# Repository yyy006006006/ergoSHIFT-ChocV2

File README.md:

# nekoko Choc V2 Edition (based on ergoSHIFT Rev1)

This derivative of ergoSHIFT Rev1 adds a PCB designed for Kailh Choc V1 / V2 switches and Choc V2 button caps.
Modified and distributed by **nekoko / [yyy006006006](https://github.com/yyy006006006)**.
This does not imply an official product or endorsement by the original author.

| Files | Description |
| --- | --- |
| [KiCad PCB source](./hardware-rev1/design_data/ergoSHIFT-rev1-ChocV1-V2-Standard-BSocket-kicad/) | Rev1-based Choc V1 / V2 PCB with the standard right-handed layout. Mount switches on the front and hot-swap sockets on the back. |
| [PCB manufacturing Gerber ZIP](./hardware-rev1/ergoSHIFT-rev1-ChocV1-V2-Standard-BSocket-gerber.zip) | Manufacturing files for this modified PCB, separate from the original Rev1 Gerbers. |
| [Choc V2 button caps](./3d-printed-buttoncaps/#choc-v2-button-caps-added-by-nekoko) | Use 14 small caps and 1 large cap. STL files, editable STEP files, and the generation script are provided. |
| [Web button configurator source](./web-configurator/) | Visual USB remapping for 11 large buttons. Requires the [nekoko configuration firmware](./firmwares_atmega32u4/LUFA/#nekoko-web-configuration-firmware-experimental) on an ATmega32U4 controller. Firmware and web app: GPL v3. |

The original Rev1 board outline, key centers, mounting holes, and MCU connections are unchanged.
This PCB is for back-mounted sockets only; direct switch soldering and reversed/left-handed assembly are not supported.
Choc V1 and V2 use different cap mounts, so choose cap files that match your switches.
The Choc V2 caps have been checked in CAD; physical printed fit and case clearance have not been tested.
See the [Rev1 notes](./hardware-rev1/#nekoko-edition-choc-v1--v2-pcb) for remaining PCB validation findings.

**Original design and license:** ergoSHIFT (c) by [mizma](https://github.com/mizma/ergoSHIFT).
This repository copies [Darudado/ergoSHIFT_RGB](https://github.com/Darudado/ergoSHIFT_RGB) at commit `8f152af28f62ab4e4357ed43b05d77b5a4bff9c2`, with the files and documentation above added on 2026-10-18.
The original designs, attribution, and license notices are retained. The PCB and cap modifications are also released under [CC BY-SA 4.0](https://creativecommons.org/licenses/by-sa/4.0/).
See [LICENSE](./LICENSE) for the full terms. Firmware and component libraries retain their respective licenses and attribution notices.

[Full license texts and notices](./LICENSES.txt) are included in source downloads. The firmware's [build instructions and bundled dependency sources](./firmwares_atmega32u4/LUFA/#source-download-and-rebuild) are provided with the modified firmware source. No personal contact information is required to download these materials.

The original repository documentation follows. Its Rev2, RGB, and reversed-assembly descriptions apply to the upstream versions, not this modified PCB.

---

ergoSHIFT arcade controller
========================================================================

_**Low profile 11 button leverless arcade controller with Acrylic shell**_

This repository contains Acrylic cut design files, PCB design files and code needed to make
an arcade controller that look like this:

Also, you can create custom artwork using the stencil provided in each hardware revision folder.

(*) Above sample Artwork based on an In-Game Screenshot + Official Fan-kit (©Cygames & ARK SYSTEM WORKS)

This controller is designed with the following concept:

* Create a reasonably compact and thin leverless arcade controller
* Layout 11 main buttons + 4 directional buttons to work with the latest 
  Capcom Pro-Tour rule-set
* Shift the home position for the main button one column to the right to better utilize the 
  more dextrous thumb and index finger instead of the little finger.
* Add the three additionally allowed buttons
* Make the button size compatible with Snackbox MICRO from [Junkfood Arcades](https://junkfoodarcades.com/)
    * I could not find good Injection molded options other than this one.
* Make the design reversible for southpaw use.
    * To assemble for left hand use, implement all buttons on the other side.
    * Controller Circuit (Pro Micro or RP2040) must be implemented on the same side
    * to compensate for the Controller Cicuitry being implemented in reverse, Acrylic layers will need to be 
      stacked in a different order and thickness.  Refer to each revision README for details

Resulting button mappings will look like this:

There are currently two revisions of the ergoSHIFT.  It uses Kailh low profile (choc v1)
mechanical keyboard switches.  The table below lists their main features.
See the README for each version for details on how to make them.

version                                 | [rev1](./hardware-rev1/)            | [rev2](./hardware-rev2/)              | [rgb](./hardware-rgb/)                | 
--------------------------------------- | ----------------------------------- | ------------------------------------- | ------------------------------------- | 
Status                                  | Verified                            | Verified                              | Verified                              | 
case dimensions                         | 233.17x147.67x14.6mm (excl. feet)   | 233.17x147.67x14.6mm (excl. feet)     | 233.17x147.67x14.6mm (excl. feet)     | 
compatibility (using provided firmware) | PC, PS3, Xinput, Switch             | PC, PS3, PS4*, PS5*, Xinput, Switch   | PC, PS3, PS4*, PS5*, Xinput, Switch   | 
add-on board                            | Sparkfun Qwiic Pro Micro            | SSD1306, SH1106 or SH1107 128x64 oled | SSD1306, SH1106 or SH1107 128x64 oled | 
onboard chip                            | -                                   | RP2040                                | RP2040                                | 
port                                    | USB-C                               | USB-C                                 | USB-C                                 | 
SMT assembly required                   | no                                  | yes                                   | yes                                   | 
OLED Support                            | no                                  | yes                                   | yes                                   | 
RGB Support                             | no                                  | no                                    | yes                                   | 
South-paw support                       | yes                                 | yes                                   | no                                    | 
firmware                                | [ATmega32U4](firmwares_atmega32u4)  | [GP2040-CE](https://gp2040-ce.info/)**| [GP2040-CE](https://gp2040-ce.info/)**| 

*) for details, see the documentation in the [GP2040-CE Console Compatibility FAQ](https://gp2040-ce.info/faq/faq-console-compatibility/)

**) Firmware is available from the official [GP2040-CE Website](https://gp2040-ce.info/downloads)
See [GP2040 firmware page](./firmware_GP2040-CE/) for firmware with ergoSHIFT specific patches (i.e. OLED display layout patch)

LICENSE
------------------------------------------------------------------------

ergoSHIFT (c) by mizma

ergoSHIFT is licensed under a
Creative Commons Attribution-ShareAlike 4.0 International License.

You should have received a copy of the license along with this
work. If not, see <https://creativecommons.org/licenses/by-sa/4.0/>.

Some portions of the work uses derivative works of other libraries and or implementations.
Firmware and hardware designs are separately licensed depending on the licensing terms of 
the works it uses.  Refer to the LICENSE files or README for the relevant terms for each
component.

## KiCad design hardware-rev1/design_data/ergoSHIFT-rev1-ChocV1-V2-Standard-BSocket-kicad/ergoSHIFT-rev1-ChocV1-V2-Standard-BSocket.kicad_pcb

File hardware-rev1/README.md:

## nekoko edition: Choc V1 / V2 PCB

For this modified PCB, use the [KiCad source](./design_data/ergoSHIFT-rev1-ChocV1-V2-Standard-BSocket-kicad/) and [Gerber ZIP](./ergoSHIFT-rev1-ChocV1-V2-Standard-BSocket-gerber.zip).
Mechanical holes for Kailh Choc V1 / V2 and a back-only socket footprint have been added, preserving the original outline, key positions, mounting holes, and MCU connections.
This is the standard right-handed layout only. Mount switches on the front and 15 Kailh CPG135001S30 sockets on the back.
Direct switch soldering is not supported, and the original reversed-assembly instructions do not apply to this version.
The MCU footprint is for an ATmega32U4 Pro Micro. Use the existing [Rev1 firmware](../firmwares_atmega32u4/), rather than the RP2040 firmware for Rev2.

Saved validation results from 2026-10-02 show 0 DRC errors, 0 unconnected items, and 0 schematic/PCB parity findings.
Remaining findings are 34 DRC warnings (6 silkscreen-to-edge clearance, 4 library footprint mismatches, and 24 silkscreen-over-copper), 1 ERC error (power pin not driven), and 21 ERC warnings.
No check exclusions were added and no rules were relaxed. These results do not establish that every physical button works or that every switch and case will fit.

Modified by nekoko / [yyy006006006](https://github.com/yyy006006006); prepared for publication on 2026-10-18.
Original design: ergoSHIFT (c) by [mizma](https://github.com/mizma/ergoSHIFT). The modified design is also licensed under [CC BY-SA 4.0](https://creativecommons.org/licenses/by-sa/4.0/).
The original Rev1 documentation follows.

---

ergoSHIFT rev1
========================================================================

This is rev1 of the ergoSHIFT.  In this version an Arduino Pro Micro
is soldered onto the main PCB.

To make one you will need:

* [acrylic shell](./acrylic-shell/)
    * For Standard Layout
        * Layers 1, 2, 4: 3mm
        * Layers 3, 5: 2mm
    * For Reverse Layout (Left handed)
        * Layers 1, 2, 3: 3mm
        * Layers 4, 5: 2mm
* [the ergoSHIFT PCB](./pcb/)
* Arduino Pro Micro [SparkFun Qwiic Pro Micro - USB-C (ATmega32U4)](https://www.sparkfun.com/products/15795)
* 15x Kailh low profile (choc v1) switches of your choice
    * I use Kailh Choc v1 Red Pro (Linear and low activation force: 35±10gf with actuation travel: 1.5±0.5mm)
    * Light Blue (gChoc) can be used for even lower actuation force.
* (optionally) 15x Kailh low profile hotswap sockets
* Button Caps (Choose one)
    * [MICRO keycap set](https://junkfoodarcades.com/collections/micro-accessories)
        * You will need to buy two sets of Snackbox Micro keycap sets.
    * [3D printed buttoncaps](../3d-printed-buttoncaps)
* 3x 6x6x8.51mm tact switches
    * I Used [TE Connectivity 3-1825910-5](https://www.te.com/ja/product-3-1825910-5.html)
* 1x 3x6x4.3 horizontal tact switch
    * https://www.newegg.com/p/2S7-01KR-035X0
    * https://shop.yushakobo.jp/collections/all-keyboard-parts/products/a1600ed-01-1
    * [schematics](images/tactile-switch_3x6x4.3.jpg)
* 7x M3 screws (length 20mm)
    * Acryl top 2mm * 2 + 3mm = 7mm
    * PCB 1.6mm
    * Acryl bottom 3mm * 2 = 6mm
    * Rubber feet screw depth = 3mm (using rubber feet below.  adjust for your part)
    * Rubber feet total depth = 8mm (using rubber feet below.  adjust for your part)
    * M3 nut height = 2mm
    * min length = 19.6mm (using rubber feet below.  adjust for your part)
    * max length = 22.6mm (using rubber feet below.  adjust for your part)
* 7x M3 nut and acompanying rubber feet
    * Rubber feet Tochigiya [TM-TK-15](https://www.monotaro.com/p/0933/2486/?displayId=5)
    * The position of the holes are intended for feet radius of less than 8mm
* Some Tin coated wires
* a soldering iron
    * something with enough power is better 
      (i.e. [Hakko FX 600](https://www.hakko.com/japan/products/hakko_fx600_set.html))
    * I recommend changing tips to D type for most Through-hole soldering, or C type if you plan to
      solder SMT as well. (default B tips are harder to use for most PCB soldering)
    * Use 320C ~ 370C temp recommended (can be changed if you know your way around)

## Assembly Instructions

### Ordering PCB

I used [JLCPCB](https://jlcpcb.com/).  Just upload the gerber files in [pcb](pcb) and keep most parameters default.
You may change PCB Qty and PCB Color if you like.  All other parameters should be kept the same.

### Ordering Buttons

#### Snackbox Micro button caps

ergoSHIFT is compatible with Snackbox Micro button caps.

You can purchase them [HERE](https://junkfoodarcades.com/collections/micro-accessories)

#### 3D printed buttons

_**Currently verifying design**_

If you have a 3D printer, print at your own will.  Files are found [here](../3d-printed-buttoncaps/).

* [ergoSHIFT-ButtonCapBig.stl](../3d-printed-buttoncaps/ergoSHIFT-ButtonCapBig.stl) 
  is used for the thumb button. 1 board needs 1 of this button.
* [ergoSHIFT-Buttoncap.stl](../3d-printed-buttoncaps/ergoSHIFT-ButtonCapBig.stl) is used for all other buttons.
  1 board needs 14 of this button.
* [ergoSHIFT-FullSetButtonCaps.stl](../3d-printed-buttoncaps/ergoSHIFT-FullSetButtonCaps.stl) is an STL file 
  containing 1 full set of buttons + extra(26 small and 2 big.).  If your 3D printing service allows 28 or more shells, it may be cheaper to print in one batch using this STL file.
    * Print size needs to be bigger than X：99.4901mm x Y： 91.7951mm x Z： 15.0000mm
    * To accomodate for the buttons in the 100mm x 100mm x 100mm size limit in some Printing services,
      This STL file has two layers of buttons arranged on top of each other.  This type of layout is only
      possible on print technology such as SLS or MJF.  Check with your 3D Printing service.
    * If your 3D Printing service does not support this type of data, use individual cap data to print.

Insertion portion may need to be adjusted in size for your 3D Printer and settings to fit snugly to the switch.
You may use some of the printer features but if that doesn't work, you might want to edit the original model.
Model data are found in [here](../3d-printed-buttoncaps/design_data/) in a [FreeCAD](https://www.freecadweb.org/)
file format.

Also, since the insertion portion requires a fairly tight tolerance which is not easily achieved by 3D printers,
the models are modelled slightly on the larger side.

I have had fairly good results with this model using SLS/MJF Nylon print but sometimes it is too large.
If the legs turn out too large to fit, use sandpaper to adjust the width of the legs.

#### Materials Consideration

* Nylon
    * May be a good place to start for tensile strength and good chemical stability.
    * can be pretty strong if printed using SLS process at some printing services
    * may be prone to warping.  not good for humid places.
* UV Resin
    * Also pretty strong as a material, and stronger to humidity.
    * Maybe slightly more brittle than Nylon

### Ordering Acrylic cuts

I use [Elecrow](https://www.elecrow.com/acrylic-cutting.html) to cut acrylic.

Upload the .zip file in [acrylic-shell](acrylic-shell/) to the Elecrow Acrylic cut service to order.
.Zip file includes the dxf file and the dimentions.txt file.  PDF is just for reference.

Use the following thickness:

* For Standard Layout
    * Layers 1, 2, 4: 3mm
    * Layers 3, 5: 2mm
* For Reverse Layout (Left handed)
    * Layers 1, 2, 3: 3mm
    * Layers 4, 5: 2mm

The original design file (FreeCAD file) can be found [here](./design_data/acryl-design/).

The Acrylic should look like the following (with PCB stacked)

(*) Above image is for standard layout (right handed)

### Assembly

1. Solder all the Choc v1 switches and the tactile switches.  make sure you populate the side with the logo.
    * If you populate the side with the logo on the left, the parts only goes in in the correct orientation.
        * For reverse layout, implement the buttons on the other side as shown in [this picture](images/Reverse-Layout-Solering.jpg)
    * If you use the hot-swap sockets, those will go on the back. (see silk screen on back side for orientation)
        * For hotswap sockets, pre-solder one side of the pad on PCB, place the socket, heat the pre-solder while
          pressing down on the socket to attach the socket.  After It is attached, solder the other side fully and then add more solder on the pre-soldered side.
2. Solder the Pro Micro Qwiic from the bottom side of the PCB up into the slit (USB socket should be between the cut-outs on the board, facing up) (Following instruction is how I did it.  There may be other ways) (This should NOT BE REVERSED for left hand layout)
    1.  First, mask the back side holes on the PCB with masking tape, and poke a small hole in each Through-hole with a needle. (This is to stop creating solder filets on the side the ProMicro will be soldered to.
        
    2. Insert a short (2~3cm) tin coated wire in the hole and solder onto the board.  Then cut the excess wire on the front side.

    3. Remove the masking tape.  The back side should have a flat solder filled hole with wires coming out the middle.
       
    4. Place the Pro-Micro into the wires, tape it down to place.  Also tape the entire front side of 
       the soldered through-holes so the wires don't fall when solder melts.
       
    5. Solder the Pro-Micro to the tin-coated wire.
       
3. stack the Acryl and PCB in following order: Layer 01, Layer 02, PCB, Layer 03, Layer 04 and Layer 05.
    * If you use 2 Layer 4s, the order should be 01, 02, 03, 04, 04.
4. Screw on the M3 screws with the nut on all 7 locations.  Rubber feet should be inserted at least in the 4 corners between the nut and the acrylic.

It should look like the following when assembled.

### Pro-Tip 1. Filing the Acrylic Edges

Acrylic Edges after laser cutting can be quite sharp and do not feel good.
You may want to file the edges with sandpaper (#400 is a nice place to start) to remove the edges 
on the top acrylic layer so it does not feel bad.

### Pro-Tip 2. Customizing design

You can also insert some artwork below the top acrylic layer as below:

(*) Above sample Artwork based on an In-Game Screenshot + Official Fan-kit (©Cygames & ARK SYSTEM WORKS)

Stencil for the artwork can be found below (Page size set to A4):

* [Stencil SVG](./images/ergoSHIFT-stencil.svg)
* [Stencil PNG 300dpi](./images/ergoSHIFT-stencil.png)
* [Southpaw Stencil SVG](./images/ergoSHIFT-stencil-reverse.svg)
* [Southpaw Stencil PNG 300dpi](./images/ergoSHIFT-stencil-reverse.png)

To cut the stencil, use one of the top acrylic plates as cutting guides (don't trust the acuracy
of the printed stencil mark, they are good enough to use as design guide, but not acurate enough for 
final cutting guide).  It is easy to cut if you tape the plate on top of the print and use a sharp
designers knife.

## License and Acknowlegements

PCB design licensed under [CC BY-SA 4.0](https://creativecommons.org/licenses/by-sa/4.0/) by mizma

Acrylic sandwitching shell heavily inspired by [Mille-Feuille](https://pomegd.booth.pm/items/2685530) 
by [@pomegd](https://twitter.com/pomegd)

PCB design uses the following libraries or derivatives of the design:

* [keyswitches.pretty](https://github.com/daprice/keyswitches.pretty) by [daprice](https://github.com/daprice) ([CC BY-SA 4.0](https://creativecommons.org/licenses/by-sa/4.0/))
* [ProMicroKiCad](https://github.com/Biacco42/ProMicroKiCad) by [Biacco42](https://github.com/Biacco42), derived from [teensy\_library](https://github.com/XenGi/teensy_library) by Ricardo Band ([MIT License](https://opensource.org/licenses/mit-license.php))

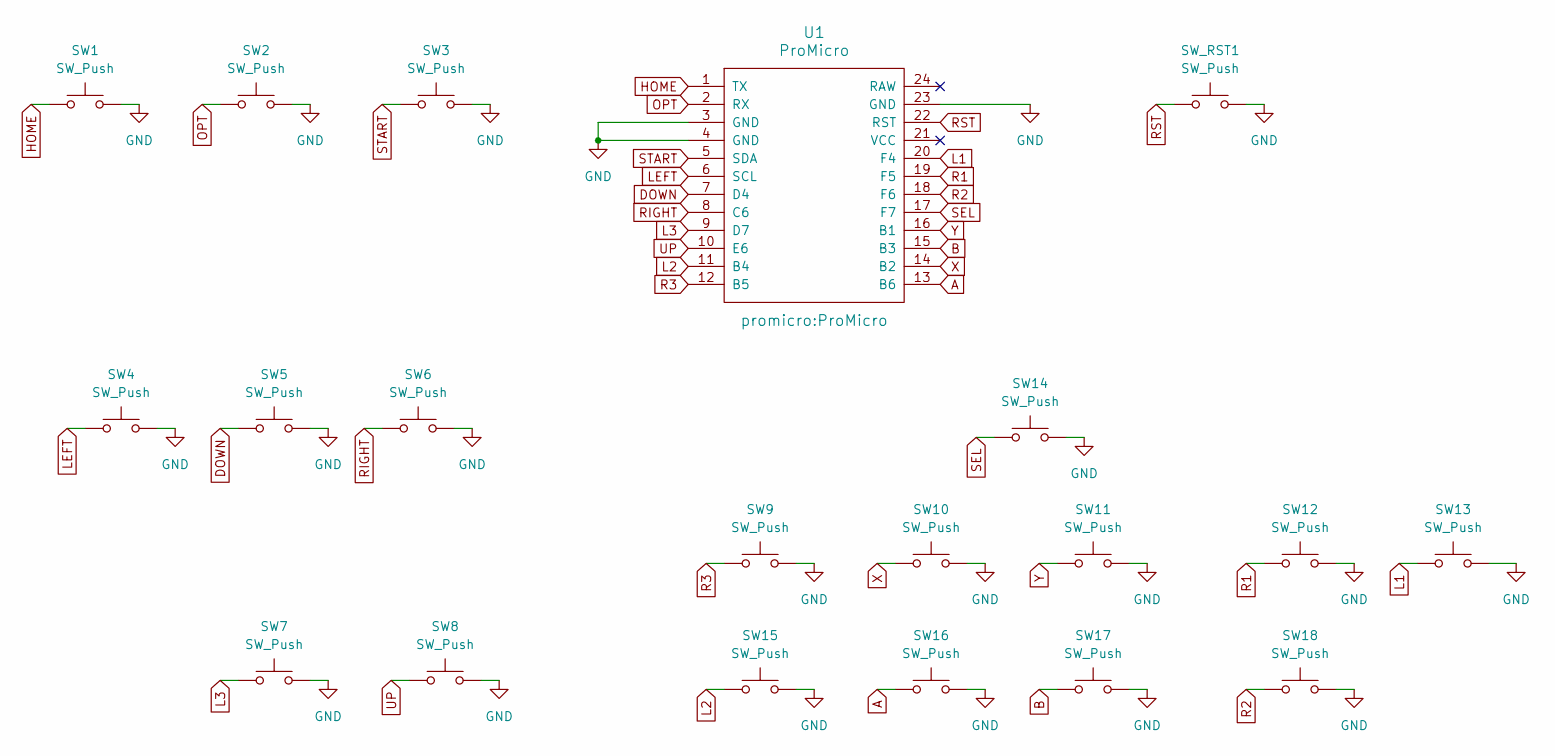
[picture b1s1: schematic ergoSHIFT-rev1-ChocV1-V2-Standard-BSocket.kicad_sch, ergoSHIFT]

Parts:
SW1, SW2, SW3: SW_Push; SW_PUSH_6mm_H8.5mm
SW4, SW5, SW6, SW7, SW8, SW9, SW10, SW11, SW12, SW13, SW14, SW15, SW16, SW17, SW18: SW_Push; SW_Choc_V1_V2_Standard_BSocket
SW_RST1: SW_Push; SW_Tactile_Yushakobo 3x6x4.3mm
U1: ProMicro

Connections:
A: SW16.1, U1.13 (B6)
B: SW17.1, U1.15 (B3)
DOWN: SW5.1, U1.7 (D4)
GND: SW1.2, SW2.2, SW3.2, SW4.2, SW5.2, SW6.2, SW7.2, SW8.2, SW9.2, SW10.2, SW11.2, SW12.2, SW13.2, SW14.2, SW15.2, SW16.2, SW17.2, SW18.2, SW_RST1.2, U1.3 (GND), U1.4 (GND), U1.23 (GND)
HOME: SW1.1, U1.1 (TX)
L1: SW13.1, U1.20 (F4)
L2: SW15.1, U1.11 (B4)
L3: SW7.1, U1.9 (D7)
LEFT: SW4.1, U1.6 (SCL)
OPT: SW2.1, U1.2 (RX)
R1: SW12.1, U1.19 (F5)
R2: SW18.1, U1.18 (F6)
R3: SW9.1, U1.12 (B5)
RIGHT: SW6.1, U1.8 (C6)
RST: SW_RST1.1, U1.22 (RST)
SEL: SW14.1, U1.17 (F7)
START: SW3.1, U1.5 (SDA)
UP: SW8.1, U1.10 (E6)
X: SW10.1, U1.14 (B2)
Y: SW11.1, U1.16 (B1)

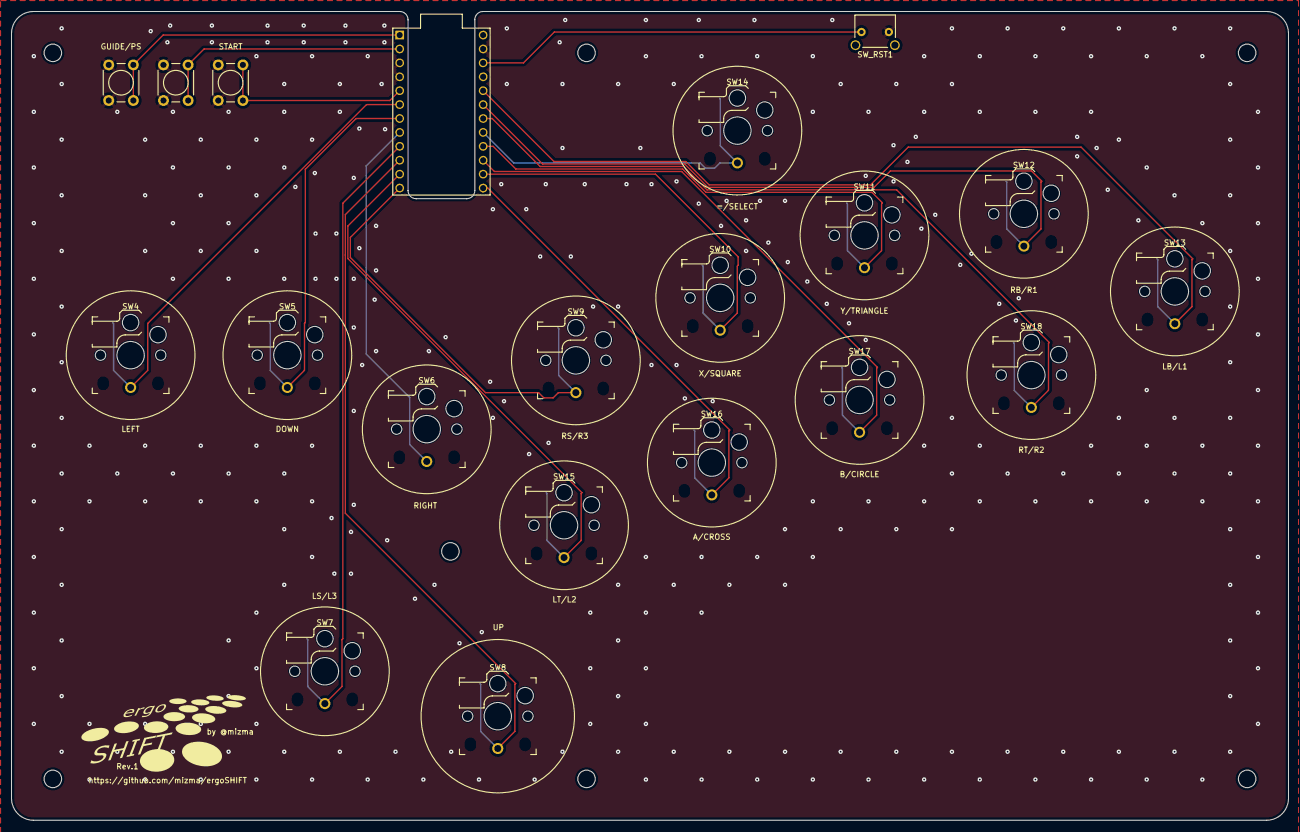
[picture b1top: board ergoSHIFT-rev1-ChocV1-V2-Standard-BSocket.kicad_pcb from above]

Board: 2 copper layers, 233.2 x 147.7 mm, 20 parts (0 on the bottom side), 20 nets.
